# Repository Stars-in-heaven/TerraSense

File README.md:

# TerraSense
Fully-open sourced soil moisture checker Im making for my mum. As <br>
I progress all the filesneeded will be made avalible here for whoever <br>
wants to make it and replicate it ( ^ . ^ )<br> <br>

### ( WIP 🚧 )<br>
<br>

| 3D MODEL        | PCB           | SCHEMATIC|
| ------------- |:-------------:| -----:|
|      |       |      |
<br>
‎ ‎ ‎ ‎ ‎ ‎ ‎ ‎ ‎ ‎ ‎ ‎ ୧‿̩͙ ˖︵ ꕀ⠀ ♱⠀ ꕀ ︵˖ ‿̩͙୨<br>
<br>

### BOM: 
| Component     | Quantity      | Links | Price |
| ------------- |:-------------:| -----:|------:|
|               |               |       |       |
|               |               |       |       |
|               |               |       |       |
<br>

### Todo List: 
- [ ] Create different folders for different versions **_(once I actually have those)_**
- [x] Start figuring out which components to use
- [x] Draft concepts, case designs, pcb layouts, ect..

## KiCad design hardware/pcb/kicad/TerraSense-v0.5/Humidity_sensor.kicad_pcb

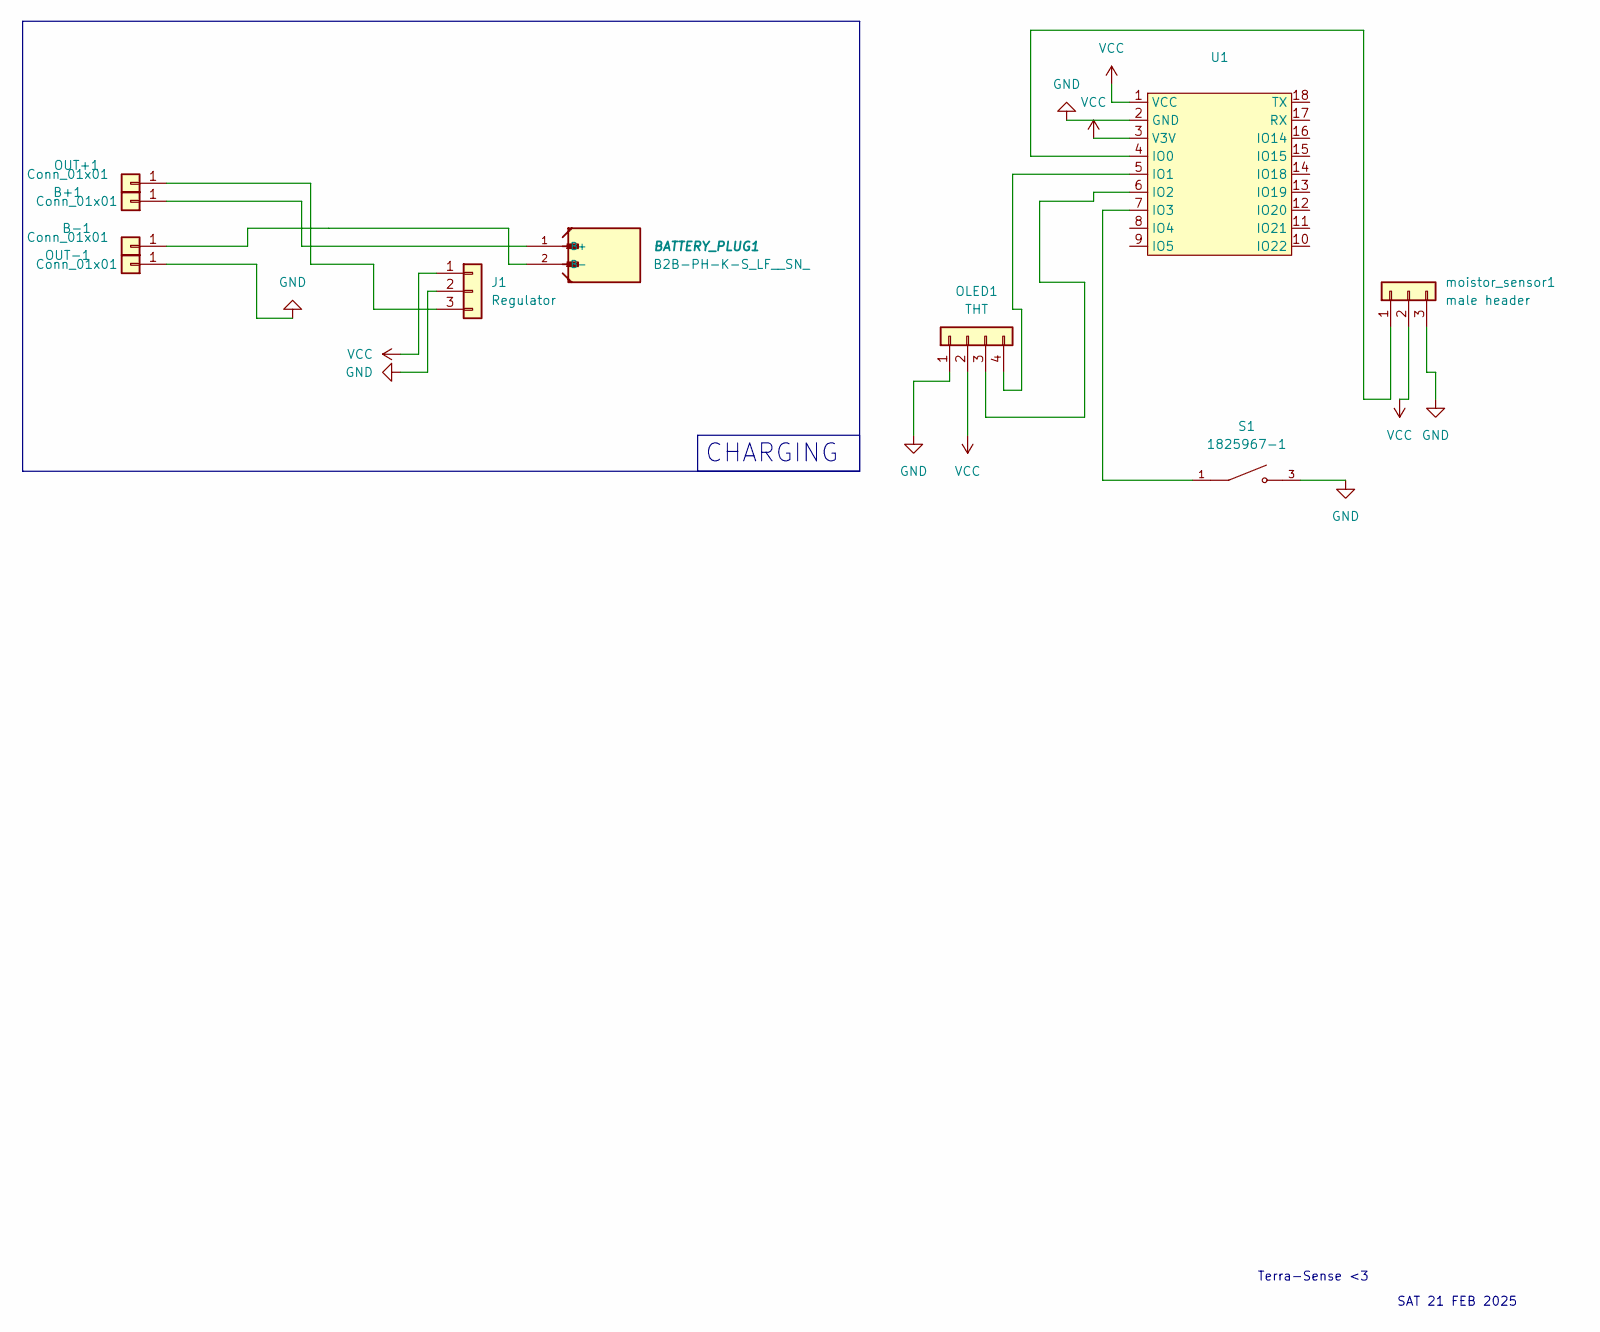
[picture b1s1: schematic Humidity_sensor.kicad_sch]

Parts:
B+1: Conn_01x01; PinHeader_1x01_P2.00mm_Vertical
B-1: Conn_01x01; PinHeader_1x01_P2.00mm_Vertical
BATTERY_PLUG1: B2B-PH-K-S_LF__SN_; JST_B2B-PH-K-S_LF__SN_
J1: Regulator; PinHeader_1x03_P2.00mm_Horizontal
OLED1: THT; PinHeader_1x04_P2.54mm_Vertical
OUT+1: Conn_01x01; PinHeader_1x01_P2.00mm_Vertical
OUT-1: Conn_01x01; PinHeader_1x01_P2.00mm_Vertical
S1: 1825967-1; regular_switch; PARTREV E
U1: Waveshare-ESP32-C6-Zero
moistor_sensor1: male header; PinHeader_1x03_P2.00mm_Horizontal

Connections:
GND: J1.2 (G), OLED1.1 (GND), OUT-1.1, S1.3, S1.4, U1.2 (GND), moistor_sensor1.3 (GND)
unnamed: B+1.1, BATTERY_PLUG1.1 (B+)
unnamed: B-1.1, BATTERY_PLUG1.2 (B-)
unnamed: J1.3 (VI), OUT+1.1
unnamed: OLED1.3 (SCL), U1.6 (IO2)
unnamed: OLED1.4 (SDA), U1.5 (IO1)
unnamed: U1.4 (IO0), moistor_sensor1.1 (AOUT)
unnamed: S1.1, S1.2, U1.7 (IO3)
VCC: J1.1 (VO), OLED1.2 (VCC), U1.1 (VCC), U1.3 (V3V), moistor_sensor1.2 (VCC)

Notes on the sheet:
SAT 21 FEB 2025
Terra-Sense <3
CHARGING

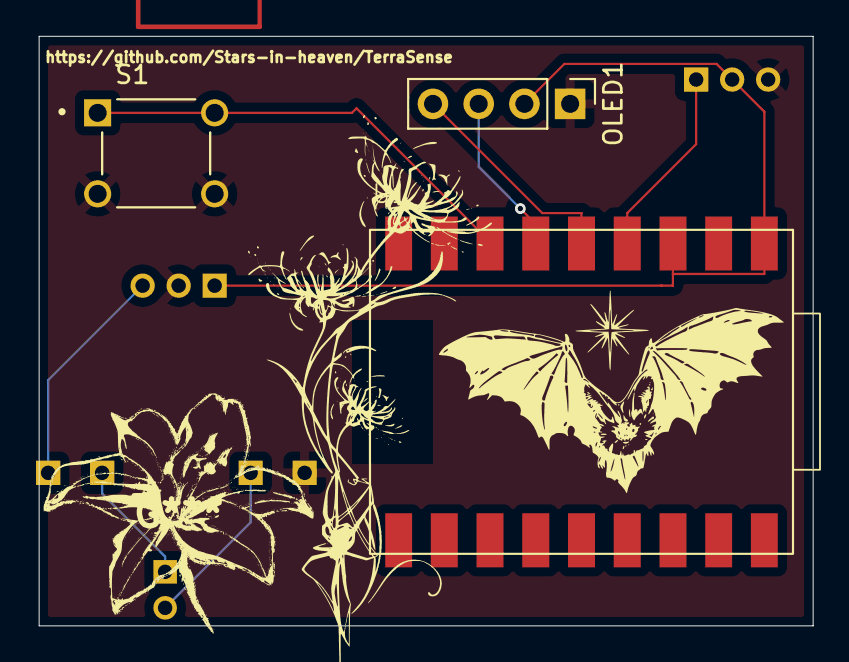
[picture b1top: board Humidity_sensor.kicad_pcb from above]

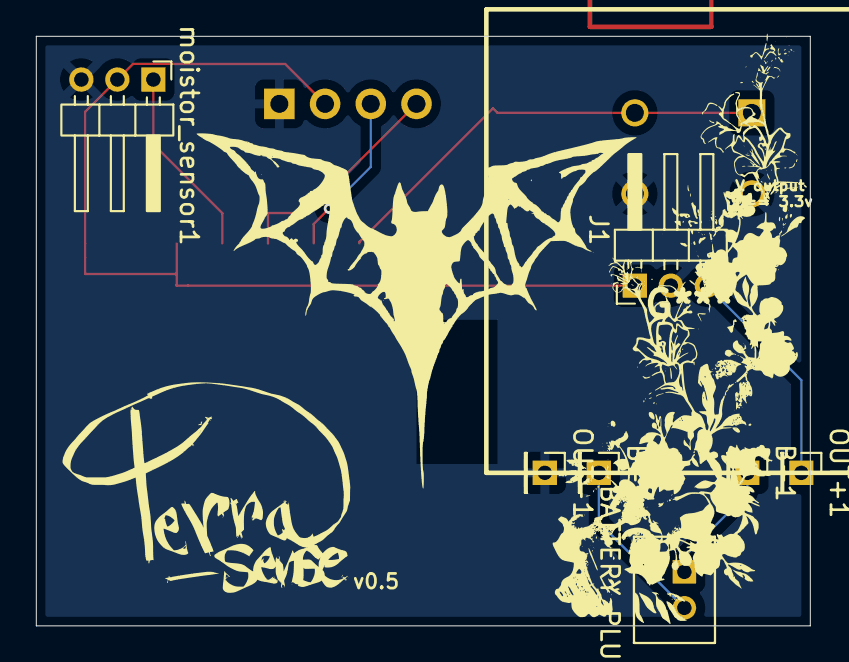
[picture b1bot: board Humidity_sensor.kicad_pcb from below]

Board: 2 copper layers, 43.0 x 32.8 mm, 10 parts (7 on the bottom side), 9 nets.

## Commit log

2026-02-20 Added devlog file for documentation
2026-02-20 Make a readme (albeit empty)
    Expanded project description and added BOM and Todo List sections.
2026-02-23 Mark components and design tasks as completed
    Updated todo list to reflect completed tasks.
2026-02-28 making folders
2026-02-28 Initial project commit with all files
2026-02-28 Add .DS_Store to .gitignore
2026-02-28 Added gitkeep.txt files to keep empty folders
